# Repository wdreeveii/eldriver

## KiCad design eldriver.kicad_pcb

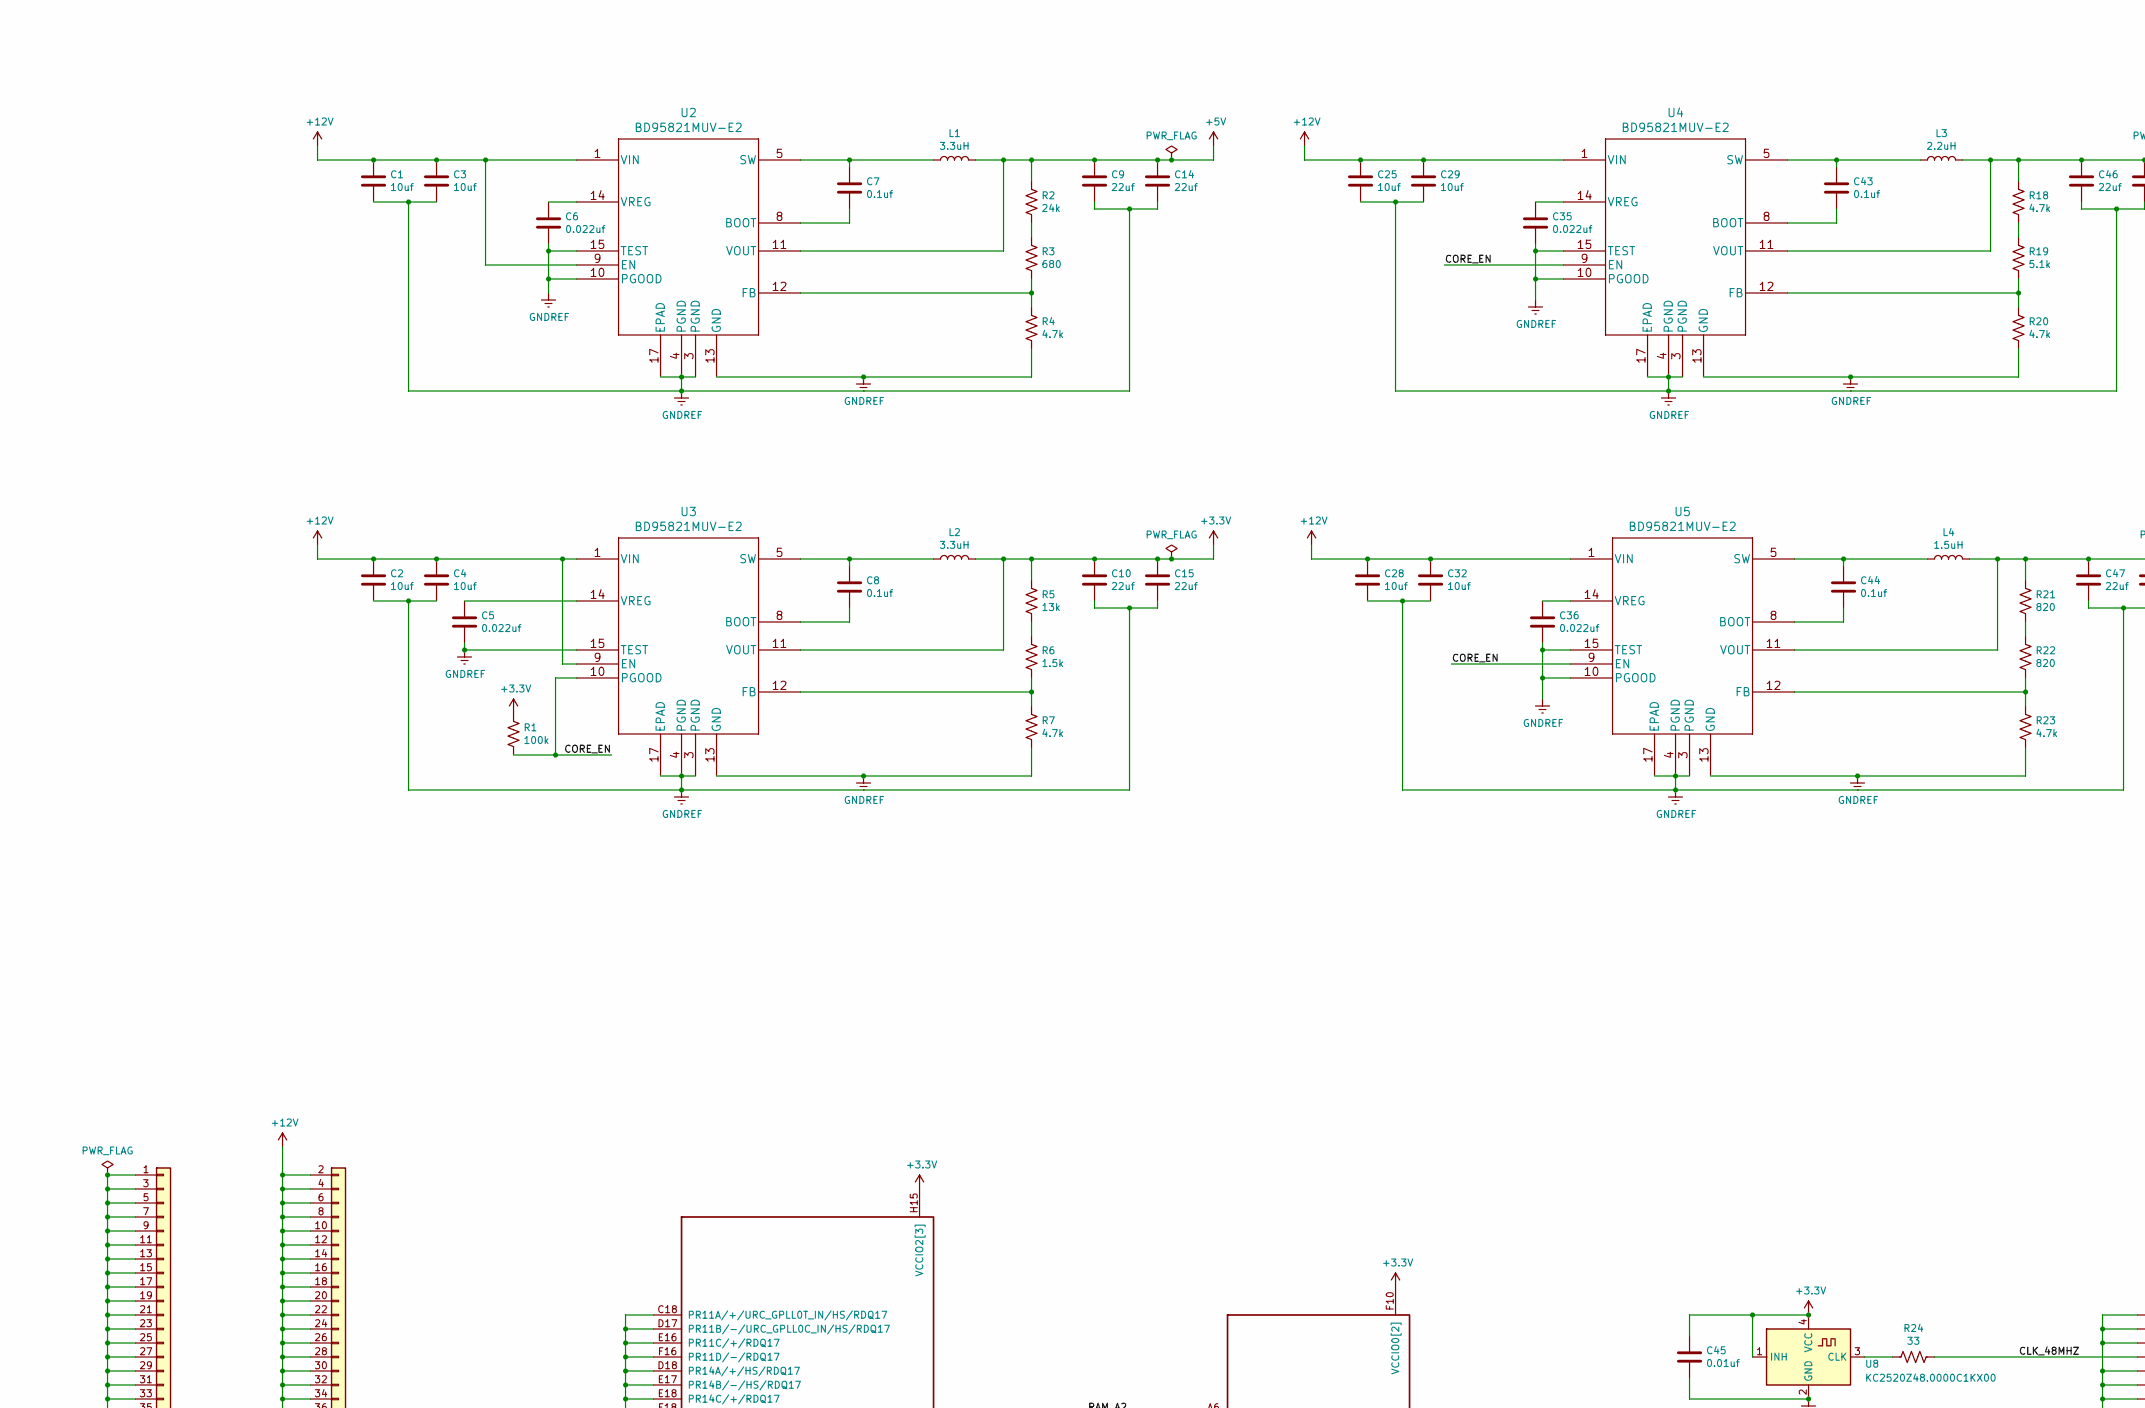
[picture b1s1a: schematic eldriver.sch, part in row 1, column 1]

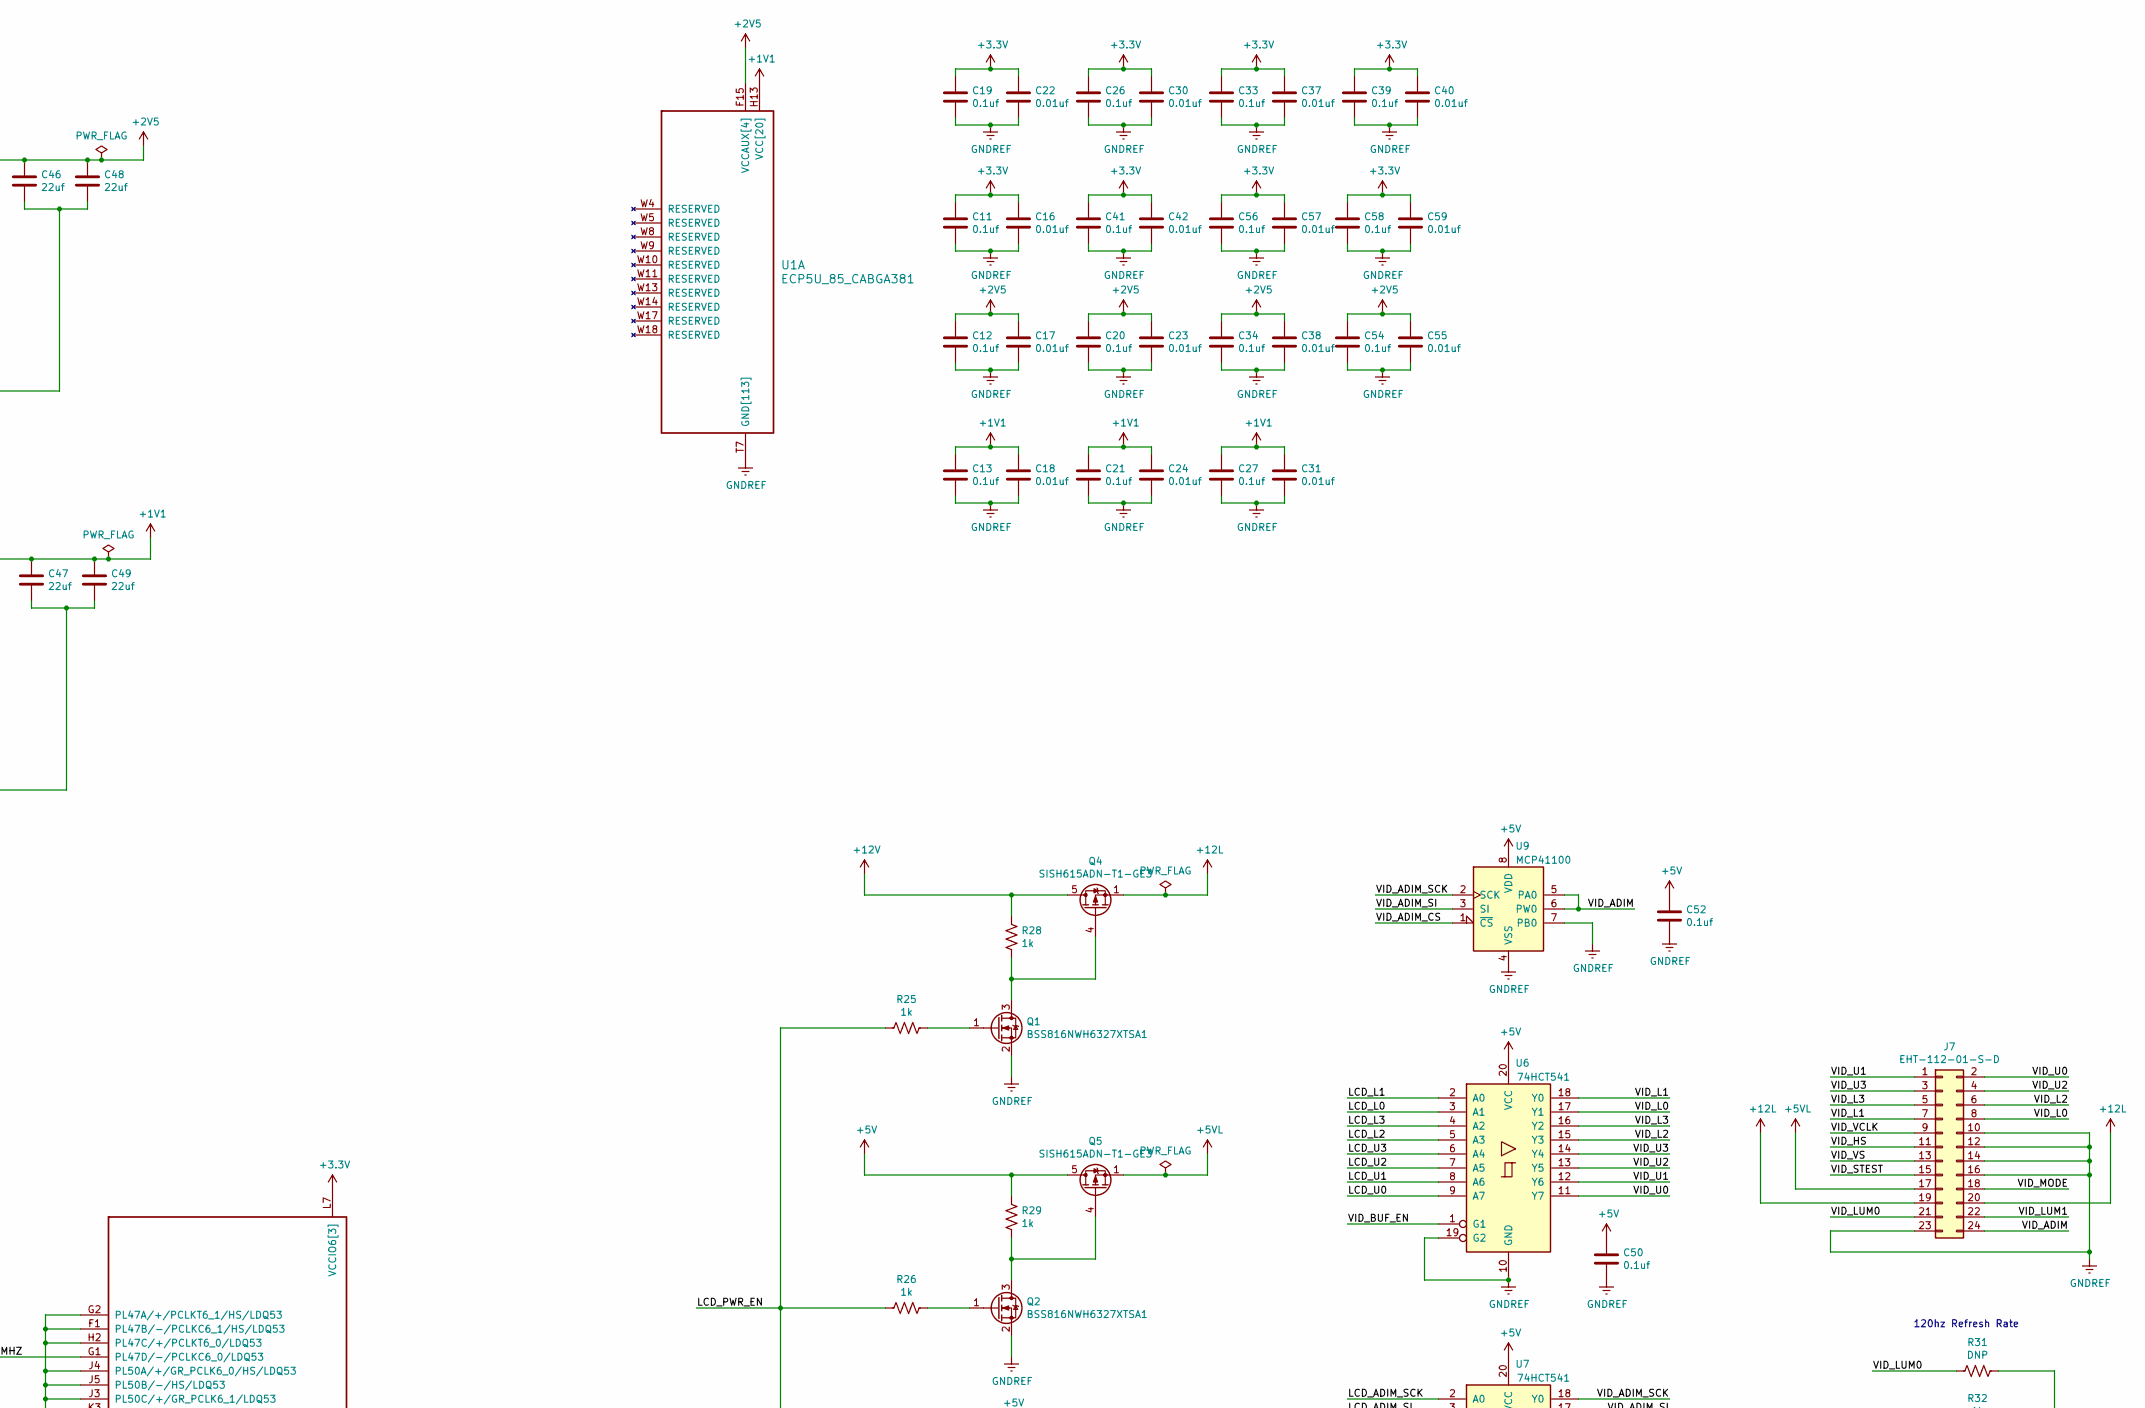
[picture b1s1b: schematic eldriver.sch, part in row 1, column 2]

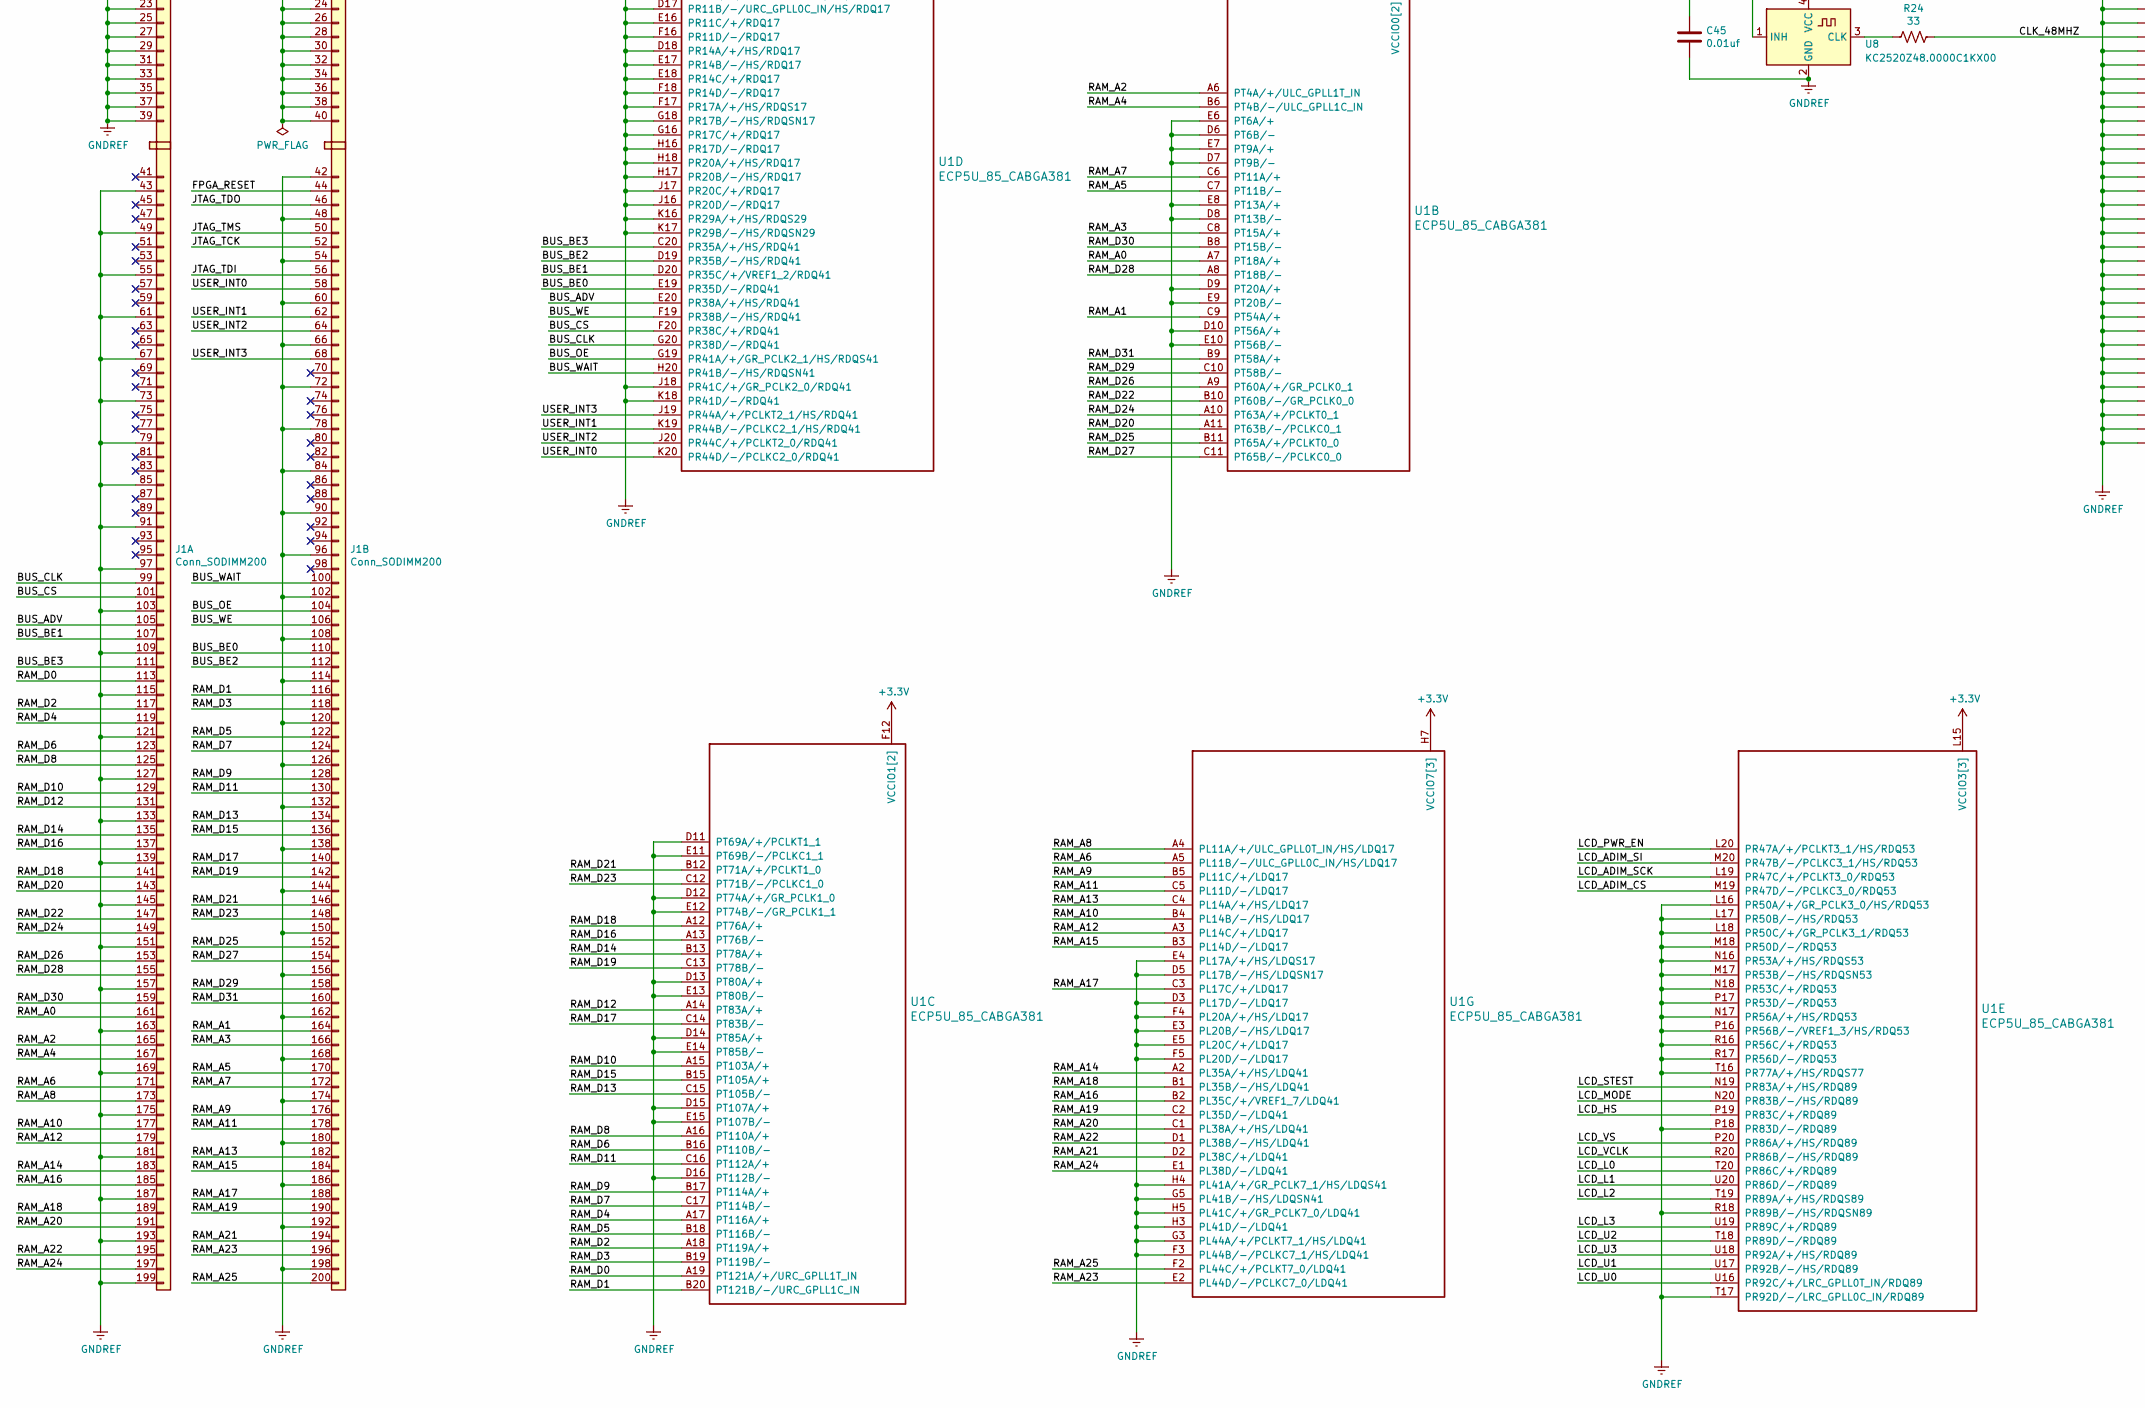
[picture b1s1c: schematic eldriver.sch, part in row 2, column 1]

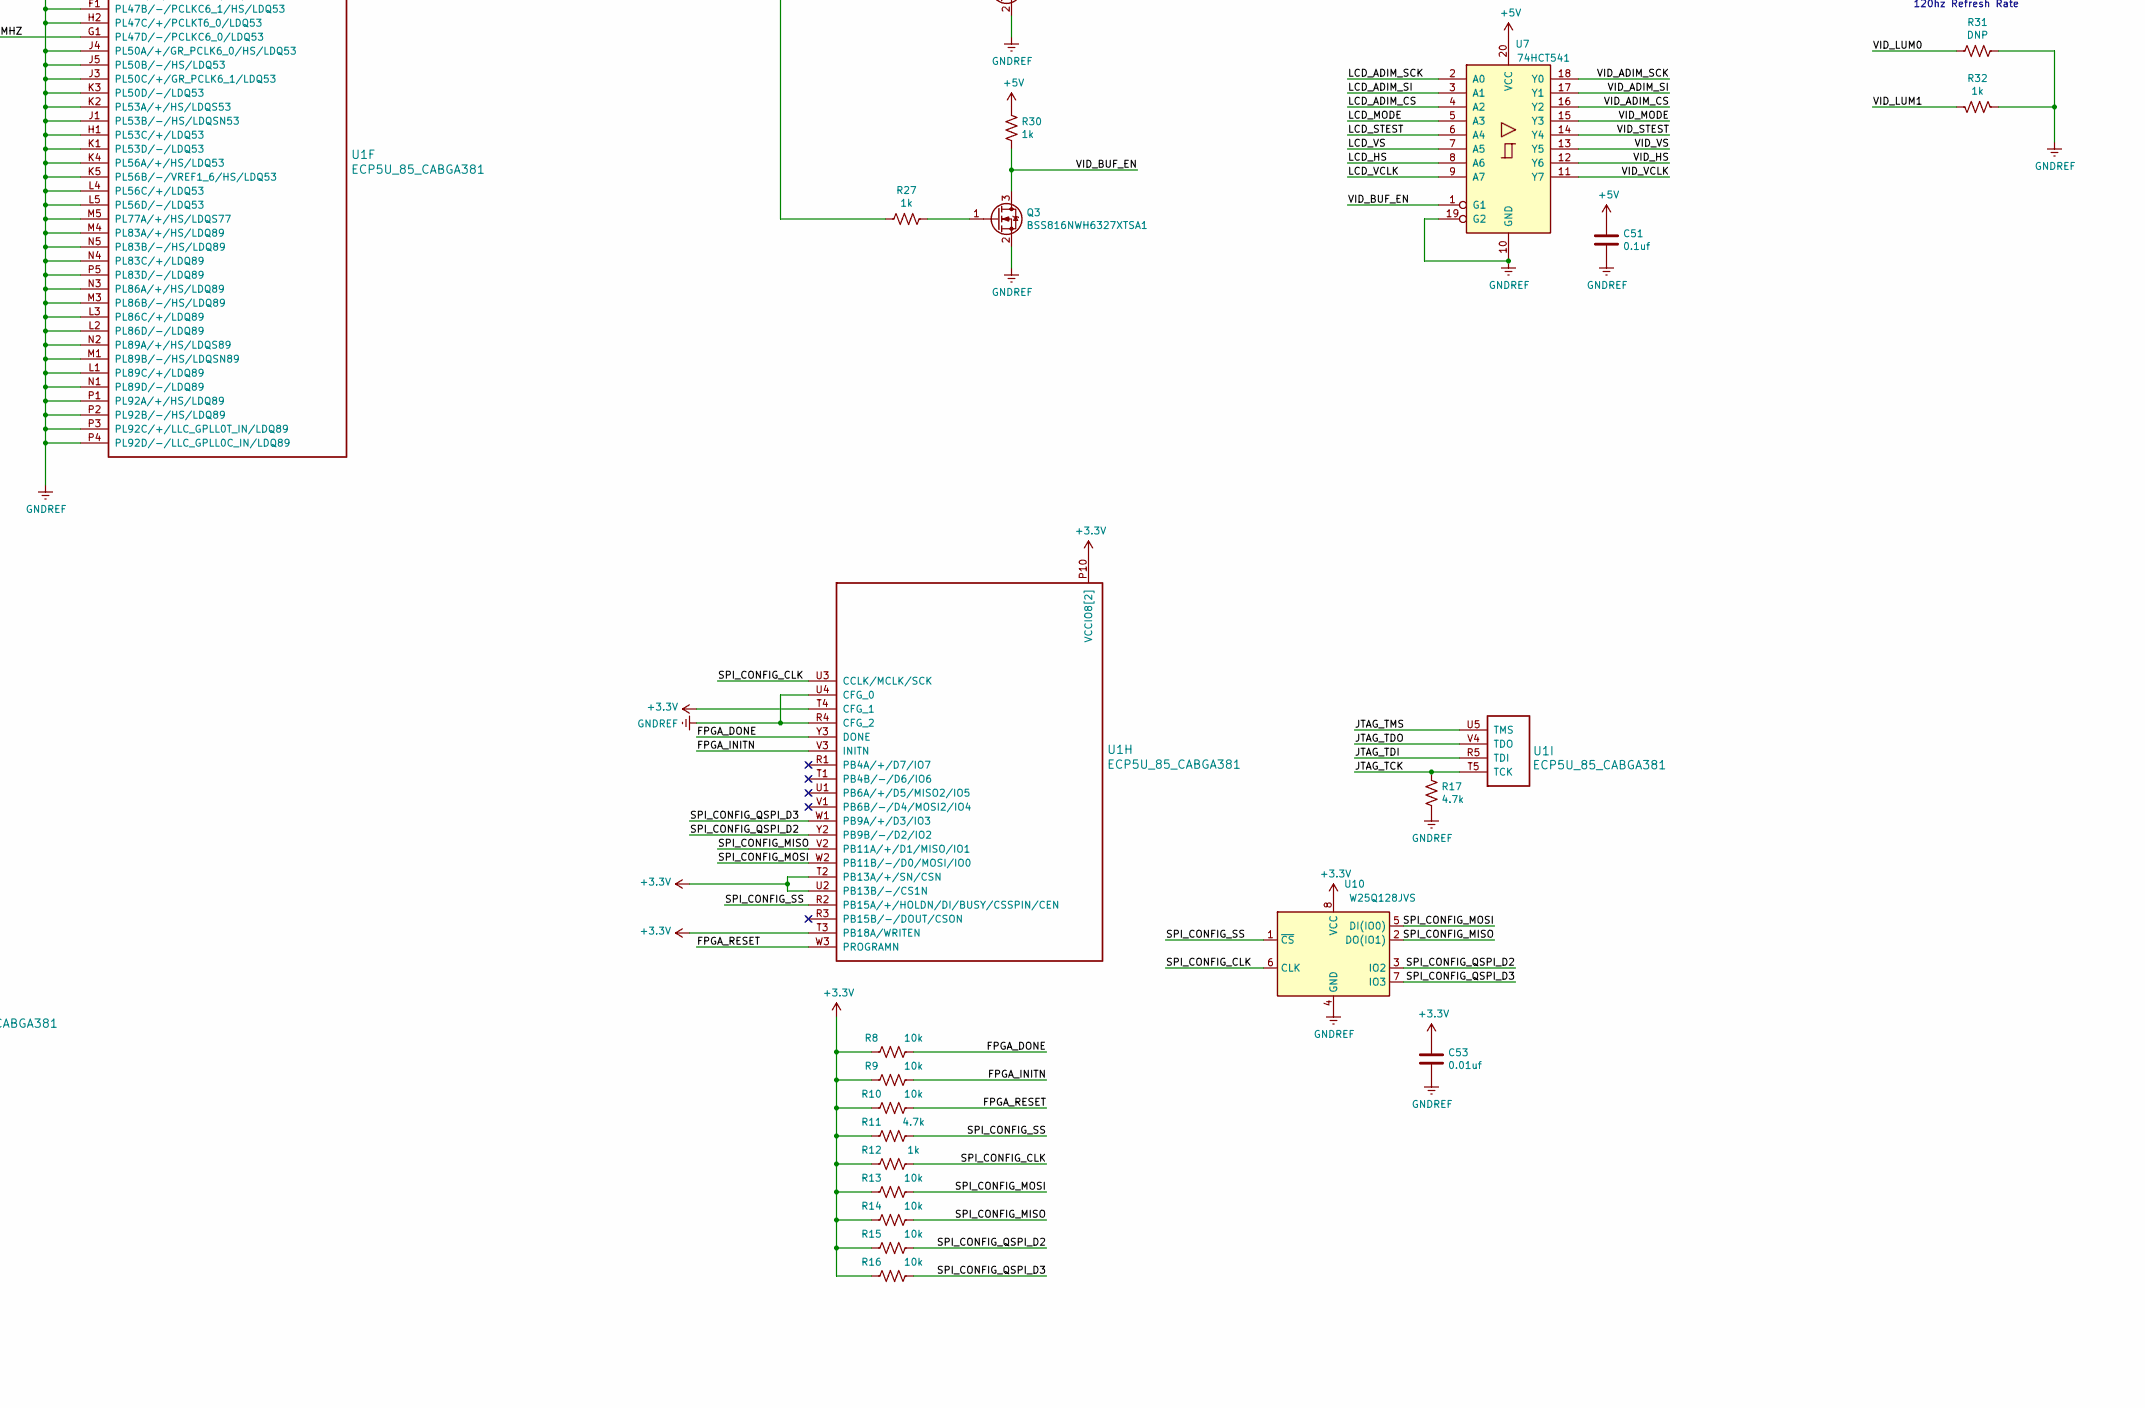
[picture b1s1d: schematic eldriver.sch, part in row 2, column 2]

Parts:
C1, C2, C3, C4, C25, C28, C29, C32: 10uf; C_0805_2012Metric
C5, C6, C35, C36: 0.022uf; C_0402_1005Metric
C7, C8, C11, C12, C13, C19, C20, C21, C26, C27, C33, C34, C39, C41, C43, C44, C50, C51, C52, C54, C56, C58: 0.1uf; C_0402_1005Metric
C9, C10, C14, C15, C46, C47, C48, C49: 22uf; C_0805_2012Metric
C16, C17, C18, C22, C23, C24, C30, C31, C37, C38, C40, C42, C45, C53, C55, C57, C59: 0.01uf; C_0402_1005Metric
J1: Conn_SODIMM200; BUS_SODIMM200DDR1
J7: EHT-112-01-S-D; SAMTEC_EHT-112-01-S-D
L1, L2: 3.3uH; L_Coilcraft_XxL4020
L3: 2.2uH; L_Coilcraft_XxL4020
L4: 1.5uH; L_Coilcraft_XxL4020
Q1, Q2, Q3: BSS816NWH6327XTSA1; SOT-323_SC-70
Q4, Q5: SISH615ADN-T1-GE3; Vishay_PowerPAK_1212-8_Single
R1: 100k; R_0603_1608Metric
R2: 24k; R_0603_1608Metric
R3: 680; R_0603_1608Metric
R4, R7, R11, R17, R18, R20, R23: 4.7k; R_0603_1608Metric
R5: 13k; R_0603_1608Metric
R6: 1.5k; R_0603_1608Metric
R8, R9, R10, R13, R14, R15, R16: 10k; R_0603_1608Metric
R12, R25, R26, R27, R28, R29, R30, R32: 1k; R_0603_1608Metric
R19: 5.1k; R_0603_1608Metric
R21, R22: 820; R_0603_1608Metric
R24: 33; R_0603_1608Metric
R31: DNP; R_0603_1608Metric
U1: ECP5U_85_CABGA381; Lattice_caBGA-381_17.0x17.0mm_Layout20x20_P0.8mm_Ball0.4mm_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
U2, U3, U4, U5: BD95821MUV-E2
U6, U7: 74HCT541; TSSOP-20_4.4x6.5mm_P0.65mm
U8: KC2520Z48.0000C1KX00; Oscillator_SMD_Kyocera_KC2520Z-4Pin_2.5x2.0mm
U9: MCP41100; SOIC-8_3.9x4.9mm_P1.27mm
U10: W25Q128JVS; SOIC-8_5.23x5.23mm_P1.27mm

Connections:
+1V1: C13.1, C18.1, C21.1, C24.1, C27.1, C31.1, C47.1, C49.1, L4.1, R21.1, U1.H8 (VCC[20]), U1.H9 (VCC[20]), U1.H10 (VCC[20]), U1.H11 (VCC[20]), U1.H12 (VCC[20]), U1.H13 (VCC[20]), U1.J8 (VCC[20]), U1.J13 (VCC[20]), U1.K8 (VCC[20]), U1.K13 (VCC[20]), U1.L8 (VCC[20]), U1.L13 (VCC[20]), U1.M8 (VCC[20]), U1.M13 (VCC[20]), U1.N8 (VCC[20]), U1.N9 (VCC[20]), U1.N10 (VCC[20]), U1.N11 (VCC[20]), U1.N12 (VCC[20]), U1.N13 (VCC[20]), U5.11 (VOUT)
+2V5: C12.1, C17.1, C20.1, C23.1, C34.1, C38.1, C46.1, C48.1, C54.1, C55.1, L3.1, R18.1, U1.F6 (VCCAUX[4]), U1.F15 (VCCAUX[4]), U1.P6 (VCCAUX[4]), U1.P15 (VCCAUX[4]), U4.11 (VOUT)
+3V3: C10.1, C11.1, C15.1, C16.1, C19.1, C22.1, C26.1, C30.1, C33.1, C37.1, C39.1, C40.1, C41.1, C42.1, C45.1, C53.1, C56.1, C57.1, C58.1, C59.1, L2.1, R1.1, R5.1, R8.2, R9.2, R10.2, R11.2, R12.2, R13.2, R14.2, R15.2, R16.2, U1.F9 (VCCIO0[2]), U1.F10 (VCCIO0[2]), U1.F11 (VCCIO1[2]), U1.F12 (VCCIO1[2]), U1.H6 (VCCIO7[3]), U1.H7 (VCCIO7[3]), U1.H14 (VCCIO2[3]), U1.H15 (VCCIO2[3]), U1.J6 (VCCIO7[3]), U1.J15 (VCCIO2[3]), U1.L6 (VCCIO6[3]), U1.L7 (VCCIO6[3]), U1.L14 (VCCIO3[3]), U1.L15 (VCCIO3[3]), U1.M6 (VCCIO6[3]), U1.M15 (VCCIO3[3]), U1.P9 (VCCIO8[2]), U1.P10 (VCCIO8[2]), U1.T2 (PB13A/+/SN/CSN), U1.T3 (PB18A/WRITEN), U1.T4 (CFG_1), U1.U2 (PB13B/-/CS1N), U3.11 (VOUT), U8.1 (INH), U8.4 (VCC), U10.8 (VCC)
+5V: C9.1, C14.1, C50.1, C51.1, C52.1, L1.1, Q5.5 (D), R2.1, R29.1, R30.1, U2.11 (VOUT), U6.20 (VCC), U7.20 (VCC), U9.8 (VDD)
+5VL: J7.17, Q5.1 (S), Q5.2 (S), Q5.3 (S)
+12L: J7.19, J7.20, Q4.1 (S), Q4.2 (S), Q4.3 (S)
+12V: C1.1, C2.1, C3.1, C4.1, C25.1, C28.1, C29.1, C32.1, J1.2, J1.4, J1.6, J1.8, J1.10, J1.12, J1.14, J1.16, J1.18, J1.20, J1.22, J1.24, J1.26, J1.28, J1.30, J1.32, J1.34, J1.36, J1.38, J1.40, Q4.5 (D), R28.1, U2.1 (VIN), U2.2 (VIN), U2.9 (EN), U2.16 (VIN), U3.1 (VIN), U3.2 (VIN), U3.9 (EN), U3.16 (VIN), U4.1 (VIN), U4.2 (VIN), U4.16 (VIN), U5.1 (VIN), U5.2 (VIN), U5.16 (VIN)
/BUS_ADV: J1.105, U1.E20 (PR38A/+/HS/RDQ41)
/BUS_BE0: J1.110, U1.E19 (PR35D/-/RDQ41)
/BUS_BE1: J1.107, U1.D20 (PR35C/+/VREF1_2/RDQ41)
/BUS_BE2: J1.112, U1.D19 (PR35B/-/HS/RDQ41)
/BUS_BE3: J1.111, U1.C20 (PR35A/+/HS/RDQ41)
/BUS_CLK: J1.99, U1.G20 (PR38D/-/RDQ41)
/BUS_CS: J1.101, U1.F20 (PR38C/+/RDQ41)
/BUS_OE: J1.104, U1.G19 (PR41A/+/GR_PCLK2_1/HS/RDQS41)
/BUS_WAIT: J1.100, U1.H20 (PR41B/-/HS/RDQSN41)
/BUS_WE: J1.106, U1.F19 (PR38B/-/HS/RDQ41)
/CLK_48MHZ: R24.1, U1.G1 (PL47D/-/PCLKC6_0/LDQ53)
/CORE_EN: R1.2, U3.10 (PGOOD), U4.9 (EN), U5.9 (EN)
/FPGA_DONE: R8.1, U1.Y3 (DONE)
/FPGA_INITN: R9.1, U1.V3 (INITN)
/FPGA_RESET: J1.44, R10.1, U1.W3 (PROGRAMN)
/JTAG_TCK: J1.52, R17.1, U1.T5 (TCK)
/JTAG_TDI: J1.56, U1.R5 (TDI)
/JTAG_TDO: J1.46, U1.V4 (TDO)
/JTAG_TMS: J1.50, U1.U5 (TMS)
/LCD_ADIM_CS: U1.M19 (PR47D/-/PCLKC3_0/RDQ53), U7.4 (A2)
/LCD_ADIM_SCK: U1.L19 (PR47C/+/PCLKT3_0/RDQ53), U7.2 (A0)
/LCD_ADIM_SI: U1.M20 (PR47B/-/PCLKC3_1/HS/RDQ53), U7.3 (A1)
/LCD_HS: U1.P19 (PR83C/+/RDQ89), U7.8 (A6)
/LCD_L0: U1.T20 (PR86C/+/RDQ89), U6.3 (A1)
/LCD_L1: U1.U20 (PR86D/-/RDQ89), U6.2 (A0)
/LCD_L2: U1.T19 (PR89A/+/HS/RDQS89), U6.5 (A3)
/LCD_L3: U1.U19 (PR89C/+/RDQ89), U6.4 (A2)
/LCD_MODE: U1.N20 (PR83B/-/HS/RDQ89), U7.5 (A3)
/LCD_PWR_EN: R25.2, R26.2, R27.2, U1.L20 (PR47A/+/PCLKT3_1/HS/RDQ53)
/LCD_STEST: U1.N19 (PR83A/+/HS/RDQ89), U7.6 (A4)
/LCD_U0: U1.U16 (PR92C/+/LRC_GPLL0T_IN/RDQ89), U6.9 (A7)
/LCD_U1: U1.U17 (PR92B/-/HS/RDQ89), U6.8 (A6)
/LCD_U2: U1.T18 (PR89D/-/RDQ89), U6.7 (A5)
/LCD_U3: U1.U18 (PR92A/+/HS/RDQ89), U6.6 (A4)
/LCD_VCLK: U1.R20 (PR86B/-/HS/RDQ89), U7.9 (A7)
/LCD_VS: U1.P20 (PR86A/+/HS/RDQ89), U7.7 (A5)
/RAM_A0: J1.161, U1.A7 (PT18A/+)
/RAM_A1: J1.164, U1.C9 (PT54A/+)
/RAM_A2: J1.165, U1.A6 (PT4A/+/ULC_GPLL1T_IN)
/RAM_A3: J1.166, U1.C8 (PT15A/+)
/RAM_A4: J1.167, U1.B6 (PT4B/-/ULC_GPLL1C_IN)
/RAM_A5: J1.170, U1.C7 (PT11B/-)
/RAM_A6: J1.171, U1.A5 (PL11B/-/ULC_GPLL0C_IN/HS/LDQ17)
/RAM_A7: J1.172, U1.C6 (PT11A/+)
/RAM_A8: J1.173, U1.A4 (PL11A/+/ULC_GPLL0T_IN/HS/LDQ17)
/RAM_A9: J1.176, U1.B5 (PL11C/+/LDQ17)
/RAM_A10: J1.177, U1.B4 (PL14B/-/HS/LDQ17)
/RAM_A11: J1.178, U1.C5 (PL11D/-/LDQ17)
/RAM_A12: J1.179, U1.A3 (PL14C/+/LDQ17)
/RAM_A13: J1.182, U1.C4 (PL14A/+/HS/LDQ17)
/RAM_A14: J1.183, U1.A2 (PL35A/+/HS/LDQ41)
/RAM_A15: J1.184, U1.B3 (PL14D/-/LDQ17)
/RAM_A16: J1.185, U1.B2 (PL35C/+/VREF1_7/LDQ41)
/RAM_A17: J1.188, U1.C3 (PL17C/+/LDQ17)
/RAM_A18: J1.189, U1.B1 (PL35B/-/HS/LDQ41)
/RAM_A19: J1.190, U1.C2 (PL35D/-/LDQ41)
/RAM_A20: J1.191, U1.C1 (PL38A/+/HS/LDQ41)
/RAM_A21: J1.194, U1.D2 (PL38C/+/LDQ41)
/RAM_A22: J1.195, U1.D1 (PL38B/-/HS/LDQ41)
/RAM_A23: J1.196, U1.E2 (PL44D/-/PCLKC7_0/LDQ41)
/RAM_A24: J1.197, U1.E1 (PL38D/-/LDQ41)
/RAM_A25: J1.200, U1.F2 (PL44C/+/PCLKT7_0/LDQ41)
/RAM_D0: J1.113, U1.A19 (PT121A/+/URC_GPLL1T_IN)
/RAM_D1: J1.116, U1.B20 (PT121B/-/URC_GPLL1C_IN)
/RAM_D2: J1.117, U1.A18 (PT119A/+)
/RAM_D3: J1.118, U1.B19 (PT119B/-)
/RAM_D4: J1.119, U1.A17 (PT116A/+)
/RAM_D5: J1.122, U1.B18 (PT116B/-)
/RAM_D6: J1.123, U1.B16 (PT110B/-)
/RAM_D7: J1.124, U1.C17 (PT114B/-)
/RAM_D8: J1.125, U1.A16 (PT110A/+)
/RAM_D9: J1.128, U1.B17 (PT114A/+)
/RAM_D10: J1.129, U1.A15 (PT103A/+)
/RAM_D11: J1.130, U1.C16 (PT112A/+)
/RAM_D12: J1.131, U1.A14 (PT83A/+)
/RAM_D13: J1.134, U1.C15 (PT105B/-)
/RAM_D14: J1.135, U1.B13 (PT78A/+)
/RAM_D15: J1.136, U1.B15 (PT105A/+)
/RAM_D16: J1.137, U1.A13 (PT76B/-)
/RAM_D17: J1.140, U1.C14 (PT83B/-)
/RAM_D18: J1.141, U1.A12 (PT76A/+)
/RAM_D19: J1.142, U1.C13 (PT78B/-)
/RAM_D20: J1.143, U1.A11 (PT63B/-/PCLKC0_1)
/RAM_D21: J1.146, U1.B12 (PT71A/+/PCLKT1_0)
/RAM_D22: J1.147, U1.B10 (PT60B/-/GR_PCLK0_0)
/RAM_D23: J1.148, U1.C12 (PT71B/-/PCLKC1_0)
/RAM_D24: J1.149, U1.A10 (PT63A/+/PCLKT0_1)
/RAM_D25: J1.152, U1.B11 (PT65A/+/PCLKT0_0)
/RAM_D26: J1.153, U1.A9 (PT60A/+/GR_PCLK0_1)
/RAM_D27: J1.154, U1.C11 (PT65B/-/PCLKC0_0)
/RAM_D28: J1.155, U1.A8 (PT18B/-)
/RAM_D29: J1.158, U1.C10 (PT58B/-)
/RAM_D30: J1.159, U1.B8 (PT15B/-)
/RAM_D31: J1.160, U1.B9 (PT58A/+)
/SPI_CONFIG_CLK: R12.1, U1.U3 (CCLK/MCLK/SCK), U10.6 (CLK)
/SPI_CONFIG_MISO: R14.1, U1.V2 (PB11A/+/D1/MISO/IO1), U10.2 (DO(IO1))
/SPI_CONFIG_MOSI: R13.1, U1.W2 (PB11B/-/D0/MOSI/IO0), U10.5 (DI(IO0))
/SPI_CONFIG_QSPI_D2: R15.1, U1.Y2 (PB9B/-/D2/IO2), U10.3 (IO2)
/SPI_CONFIG_QSPI_D3: R16.1, U1.W1 (PB9A/+/D3/IO3), U10.7 (IO3)
/SPI_CONFIG_SS: R11.1, U1.R2 (PB15A/+/HOLDN/DI/BUSY/CSSPIN/CEN), U10.1 (~CS)
/USER_INT0: J1.58, U1.K20 (PR44D/-/PCLKC2_0/RDQ41)
/USER_INT1: J1.62, U1.K19 (PR44B/-/PCLKC2_1/HS/RDQ41)
/USER_INT2: J1.64, U1.J20 (PR44C/+/PCLKT2_0/RDQ41)
/USER_INT3: J1.68, U1.J19 (PR44A/+/PCLKT2_1/HS/RDQ41)
/VID_ADIM: J7.24, U9.5 (PA0), U9.6 (PW0)
/VID_ADIM_CS: U7.16 (Y2), U9.1 (~CS)
/VID_ADIM_SCK: U7.18 (Y0), U9.2 (SCK)
/VID_ADIM_SI: U7.17 (Y1), U9.3 (SI)
/VID_BUF_EN: Q3.3 (D), R30.2, U6.1 (G1), U7.1 (G1)
/VID_HS: J7.11, U7.12 (Y6)
/VID_L0: J7.8, U6.17 (Y1)
/VID_L1: J7.7, U6.18 (Y0)
/VID_L2: J7.6, U6.15 (Y3)
/VID_L3: J7.5, U6.16 (Y2)
/VID_LUM0: J7.21, R31.2
/VID_LUM1: J7.22, R32.2
/VID_MODE: J7.18, U7.15 (Y3)
/VID_STEST: J7.15, U7.14 (Y4)
/VID_U0: J7.2, U6.11 (Y7)
/VID_U1: J7.1, U6.12 (Y6)
/VID_U2: J7.4, U6.13 (Y5)
/VID_U3: J7.3, U6.14 (Y4)
/VID_VCLK: J7.9, U7.11 (Y7)
/VID_VS: J7.13, U7.13 (Y5)
GNDREF: C1.2, C2.2, C3.2, C4.2, C5.2, C6.2, C9.2, C10.2, C11.2, C12.2, C13.2, C14.2, C15.2, C16.2, C17.2, C18.2, C19.2, C20.2, C21.2, C22.2, C23.2, C24.2, C25.2, C26.2, C27.2, C28.2, C29.2, C30.2, C31.2, C32.2, C33.2, C34.2, C35.2, C36.2, C37.2, C38.2, C39.2, C40.2, C41.2, C42.2, C45.2, C46.2, C47.2, C48.2, C49.2, C50.2, C51.2, C52.2, C53.2, C54.2, C55.2, C56.2, C57.2, C58.2, C59.2, J1.1, J1.3, J1.5, J1.7, J1.9, J1.11, J1.13, J1.15, J1.17, J1.19, J1.21, J1.23, J1.25, J1.27, J1.29, J1.31, J1.33, J1.35, J1.37, J1.39, J1.42, J1.43, J1.48, J1.49, J1.54, J1.55, J1.60, J1.61, J1.66, J1.67, J1.72, J1.73, J1.78, J1.79, J1.84, J1.85, J1.90, J1.91, J1.96, J1.97, J1.102, J1.103, J1.108, J1.109, J1.114, J1.115, J1.120, J1.121, J1.126, J1.127, J1.132, J1.133, J1.138, J1.139, J1.144, J1.145, J1.150, J1.151, J1.156, J1.157, J1.162, J1.163, J1.168, J1.169, J1.174, J1.175, J1.180, J1.181, J1.186, J1.187, J1.192, J1.193, J1.198, J1.199, J7.10, J7.12, J7.14, J7.16, J7.23, Q1.2 (S), Q2.2 (S), Q3.2 (S), R4.2, R7.2, R17.2, R20.2, R23.2, R31.1, R32.1, U1.B7 (GND[113]), U1.B14 (GND[113]), U1.C18 (PR11A/+/URC_GPLL0T_IN/HS/RDQ17), U1.C19 (GND[113]), U1.D3 (PL17D/-/LDQ17), U1.D4 (GND[113]), U1.D5 (PL17B/-/HS/LDQSN17), U1.D6 (PT6B/-), U1.D7 (PT9B/-), U1.D8 (PT13B/-), U1.D9 (PT20A/+), U1.D10 (PT56A/+), U1.D11 (PT69A/+/PCLKT1_1), U1.D12 (PT74A/+/GR_PCLK1_0), U1.D13 (PT80A/+), U1.D14 (PT85A/+), U1.D15 (PT107A/+), U1.D16 (PT112B/-), U1.D17 (PR11B/-/URC_GPLL0C_IN/HS/RDQ17), U1.D18 (PR14A/+/HS/RDQ17), U1.E3 (PL20B/-/HS/LDQ17), U1.E4 (PL17A/+/HS/LDQS17), U1.E5 (PL20C/+/LDQ17), U1.E6 (PT6A/+), U1.E7 (PT9A/+), U1.E8 (PT13A/+), U1.E9 (PT20B/-), U1.E10 (PT56B/-), U1.E11 (PT69B/-/PCLKC1_1), U1.E12 (PT74B/-/GR_PCLK1_1), U1.E13 (PT80B/-), U1.E14 (PT85B/-), U1.E15 (PT107B/-), U1.E16 (PR11C/+/RDQ17), U1.E17 (PR14B/-/HS/RDQ17), U1.E18 (PR14C/+/RDQ17), U1.F1 (PL47B/-/PCLKC6_1/HS/LDQ53), U1.F3 (PL44B/-/PCLKC7_1/HS/LDQ41), U1.F4 (PL20A/+/HS/LDQ17), U1.F5 (PL20D/-/LDQ17), U1.F7 (GND[113]), U1.F8 (GND[113]), U1.F13 (GND[113]), U1.F14 (GND[113]), U1.F16 (PR11D/-/RDQ17), U1.F17 (PR17A/+/HS/RDQS17), U1.F18 (PR14D/-/RDQ17), U1.G2 (PL47A/+/PCLKT6_1/HS/LDQ53), U1.G3 (PL44A/+/PCLKT7_1/HS/LDQ41), U1.G4 (GND[113]), U1.G5 (PL41B/-/HS/LDQSN41), U1.G6 (GND[113]), U1.G7 (GND[113]), U1.G8 (GND[113]), U1.G9 (GND[113]), U1.G10 (GND[113]), U1.G11 (GND[113]), U1.G12 (GND[113]), U1.G13 (GND[113]), U1.G14 (GND[113]), U1.G15 (GND[113]), U1.G16 (PR17C/+/RDQ17), U1.G17 (GND[113]), U1.G18 (PR17B/-/HS/RDQSN17), U1.H1 (PL53C/+/LDQ53), U1.H2 (PL47C/+/PCLKT6_0/LDQ53), U1.H3 (PL41D/-/LDQ41), U1.H4 (PL41A/+/GR_PCLK7_1/HS/LDQS41), U1.H5 (PL41C/+/GR_PCLK7_0/LDQ41), U1.H16 (PR17D/-/RDQ17), U1.H17 (PR20B/-/HS/RDQ17), U1.H18 (PR20A/+/HS/RDQ17), U1.H19 (GND[113]), U1.J1 (PL53B/-/HS/LDQSN53), U1.J2 (GND[113]), U1.J3 (PL50C/+/GR_PCLK6_1/LDQ53), U1.J4 (PL50A/+/GR_PCLK6_0/HS/LDQ53), U1.J5 (PL50B/-/HS/LDQ53), U1.J7 (GND[113]), U1.J9 (GND[113]), U1.J10 (GND[113]), U1.J11 (GND[113]), U1.J12 (GND[113]), U1.J14 (GND[113]), U1.J16 (PR20D/-/RDQ17), U1.J17 (PR20C/+/RDQ17), U1.J18 (PR41C/+/GR_PCLK2_0/RDQ41), U1.K1 (PL53D/-/LDQ53), U1.K2 (PL53A/+/HS/LDQS53), U1.K3 (PL50D/-/LDQ53), U1.K4 (PL56A/+/HS/LDQ53), U1.K5 (PL56B/-/VREF1_6/HS/LDQ53), U1.K6 (GND[113]), U1.K7 (GND[113]), U1.K9 (GND[113]), U1.K10 (GND[113]), U1.K11 (GND[113]), U1.K12 (GND[113]), U1.K14 (GND[113]), U1.K15 (GND[113]), U1.K16 (PR29A/+/HS/RDQS29), U1.K17 (PR29B/-/HS/RDQSN29), U1.K18 (PR41D/-/RDQ41), U1.L1 (PL89C/+/LDQ89), U1.L2 (PL86D/-/LDQ89), U1.L3 (PL86C/+/LDQ89), U1.L4 (PL56C/+/LDQ53), U1.L5 (PL56D/-/LDQ53), U1.L9 (GND[113]), U1.L10 (GND[113]), U1.L11 (GND[113]), U1.L12 (GND[113]), U1.L16 (PR50A/+/GR_PCLK3_0/HS/RDQ53), U1.L17 (PR50B/-/HS/RDQ53), U1.L18 (PR50C/+/GR_PCLK3_1/RDQ53), U1.M1 (PL89B/-/HS/LDQSN89), U1.M2 (GND[113]), U1.M3 (PL86B/-/HS/LDQ89), U1.M4 (PL83A/+/HS/LDQ89), U1.M5 (PL77A/+/HS/LDQS77), U1.M7 (GND[113]), U1.M9 (GND[113]), U1.M10 (GND[113]), U1.M11 (GND[113]), U1.M12 (GND[113]), U1.M14 (GND[113]), U1.M16 (GND[113]), U1.M17 (PR53B/-/HS/RDQSN53), U1.M18 (PR50D/-/RDQ53), U1.N1 (PL89D/-/LDQ89), U1.N2 (PL89A/+/HS/LDQS89), U1.N3 (PL86A/+/HS/LDQ89), U1.N4 (PL83C/+/LDQ89), U1.N5 (PL83B/-/HS/LDQ89), U1.N6 (GND[113]), U1.N7 (GND[113]), U1.N14 (GND[113]), U1.N15 (GND[113]), U1.N16 (PR53A/+/HS/RDQS53), U1.N17 (PR56A/+/HS/RDQ53), U1.N18 (PR53C/+/RDQ53), U1.P1 (PL92A/+/HS/LDQ89), U1.P2 (PL92B/-/HS/LDQ89), U1.P3 (PL92C/+/LLC_GPLL0T_IN/LDQ89), U1.P4 (PL92D/-/LLC_GPLL0C_IN/LDQ89), U1.P5 (PL83D/-/LDQ89), U1.P7 (GND[113]), U1.P8 (GND[113]), U1.P11 (GND[113]), U1.P12 (GND[113]), U1.P13 (GND[113]), U1.P14 (GND[113]), U1.P16 (PR56B/-/VREF1_3/HS/RDQ53), U1.P17 (PR53D/-/RDQ53), U1.P18 (PR83D/-/RDQ89), U1.R4 (CFG_2), U1.R16 (PR56C/+/RDQ53), U1.R17 (PR56D/-/RDQ53), U1.R18 (PR89B/-/HS/RDQSN89), U1.R19 (GND[113]), U1.T6 (GND[113]), U1.T7 (GND[113]), U1.T8 (GND[113]), U1.T9 (GND[113]), U1.T10 (GND[113]), U1.T11 (GND[113]), U1.T12 (GND[113]), U1.T13 (GND[113]), U1.T14 (GND[113]), U1.T15 (GND[113]), U1.T16 (PR77A/+/HS/RDQS77), U1.T17 (PR92D/-/LRC_GPLL0C_IN/RDQ89), U1.U4 (CFG_0), U1.U6 (GND[113]), U1.U7 (GND[113]), U1.U8 (GND[113]), U1.U9 (GND[113]), U1.U10 (GND[113]), U1.U11 (GND[113]), U1.U12 (GND[113]), U1.U13 (GND[113]), U1.U14 (GND[113]), U1.U15 (GND[113]), U1.V5 (GND[113]), U1.V6 (GND[113]), U1.V7 (GND[113]), U1.V8 (GND[113]), U1.V9 (GND[113]), U1.V10 (GND[113]), U1.V11 (GND[113]), U1.V12 (GND[113]), U1.V13 (GND[113]), U1.V14 (GND[113]), U1.V15 (GND[113]), U1.V16 (GND[113]), U1.V17 (GND[113]), U1.V18 (GND[113]), U1.V19 (GND[113]), U1.V20 (GND[113]), U1.W6 (GND[113]), U1.W7 (GND[113]), U1.W12 (GND[113]), U1.W15 (GND[113]), U1.W16 (GND[113]), U1.W19 (GND[113]), U1.W20 (GND[113]), U1.Y5 (GND[113]), U1.Y6 (GND[113]), U1.Y7 (GND[113]), U1.Y8 (GND[113]), U1.Y11 (GND[113]), U1.Y12 (GND[113]), U1.Y14 (GND[113]), U1.Y15 (GND[113]), U1.Y16 (GND[113]), U1.Y17 (GND[113]), U1.Y19 (GND[113]), U2.3 (PGND), U2.4 (PGND), U2.10 (PGOOD), U2.13 (GND), U2.15 (TEST)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
unnamed: C5.1, U3.14 (VREG)
unnamed: C6.1, U2.14 (VREG)
unnamed: C7.1, L1.2, U2.5 (SW), U2.6 (SW), U2.7 (SW)
unnamed: C7.2, U2.8 (BOOT)
unnamed: C8.1, L2.2, U3.5 (SW), U3.6 (SW), U3.7 (SW)
unnamed: C8.2, U3.8 (BOOT)
unnamed: C35.1, U4.14 (VREG)
unnamed: C36.1, U5.14 (VREG)
unnamed: C43.1, L3.2, U4.5 (SW), U4.6 (SW), U4.7 (SW)
unnamed: C43.2, U4.8 (BOOT)
unnamed: C44.1, L4.2, U5.5 (SW), U5.6 (SW), U5.7 (SW)
unnamed: C44.2, U5.8 (BOOT)
unnamed: Q1.1 (G), R25.1
unnamed: Q1.3 (D), Q4.4 (G), R28.2
unnamed: Q2.1 (G), R26.1
unnamed: Q2.3 (D), Q5.4 (G), R29.2
unnamed: Q3.1 (G), R27.1
unnamed: R2.2, R3.1
unnamed: R3.2, R4.1, U2.12 (FB)
unnamed: R5.2, R6.1
unnamed: R6.2, R7.1, U3.12 (FB)
unnamed: R18.2, R19.1
unnamed: R19.2, R20.1, U4.12 (FB)
unnamed: R21.2, R22.1
unnamed: R22.2, R23.1, U5.12 (FB)
unnamed: R24.2, U8.3 (CLK)

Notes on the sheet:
120hz Refresh Rate

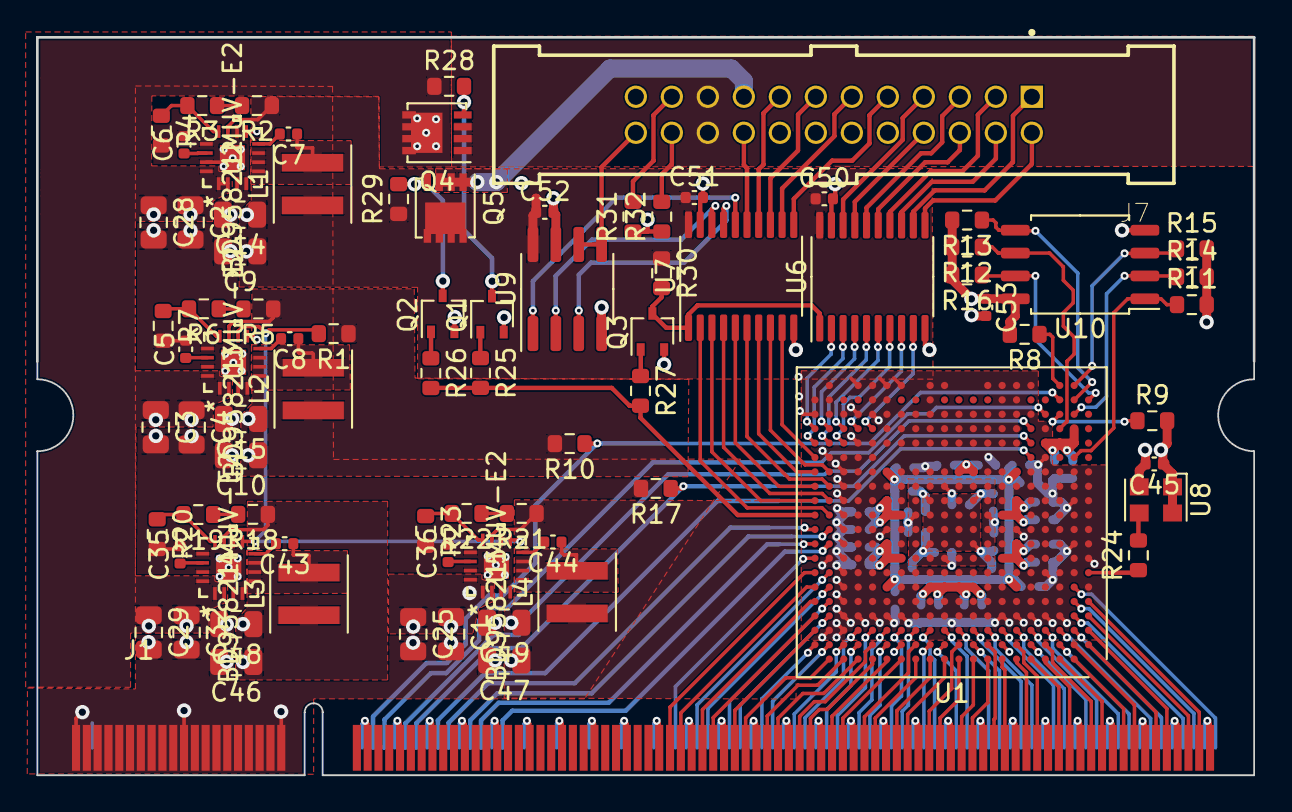
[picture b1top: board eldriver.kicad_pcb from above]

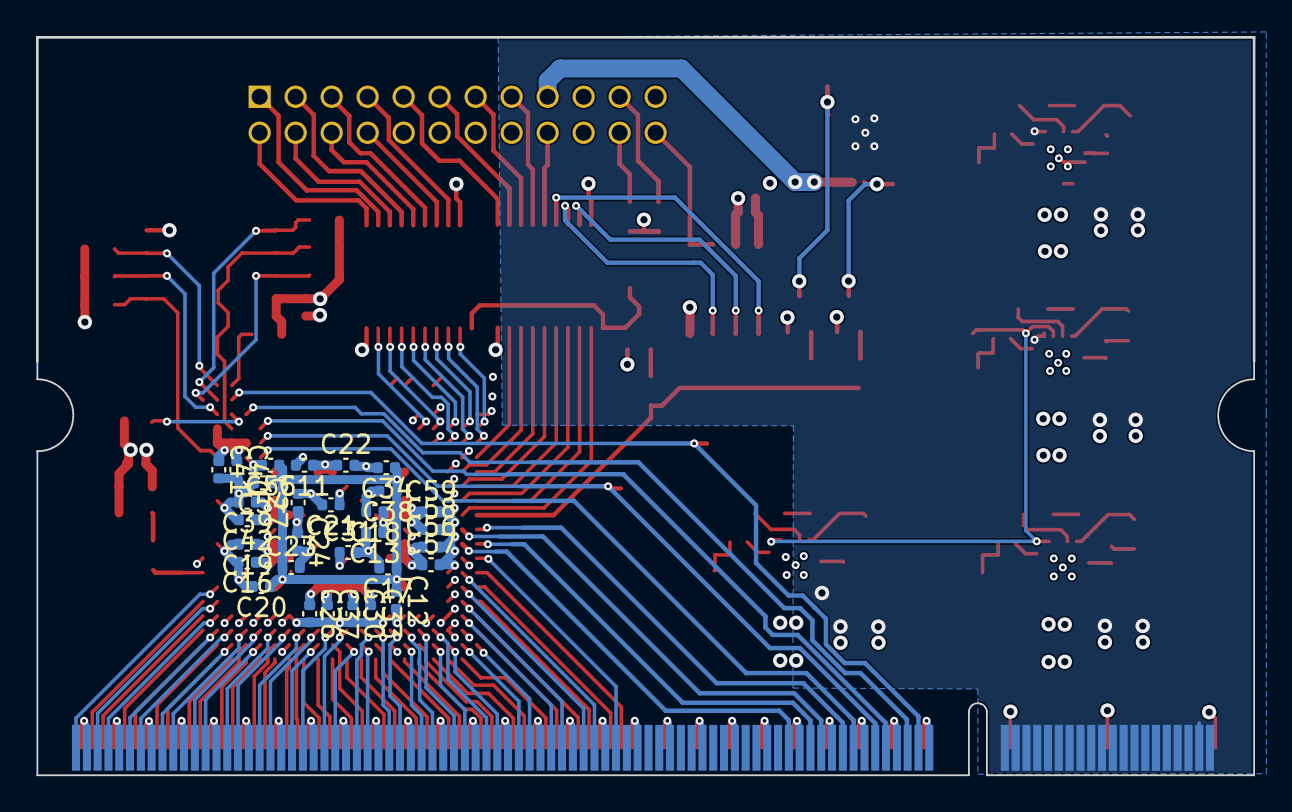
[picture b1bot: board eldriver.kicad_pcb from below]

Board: 6 copper layers, 67.6 x 41.0 mm, 112 parts (30 on the bottom side), 158 nets.
